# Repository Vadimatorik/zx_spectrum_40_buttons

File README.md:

# zx_spectrum_40_buttons
Репозиторий содержит в себе файлы проекта и файлы производства клавиатуры в 40 клавиш для подключения к ZX Spectrum совместимым компьютерам. В качестве клавиш используются Cherry MX.

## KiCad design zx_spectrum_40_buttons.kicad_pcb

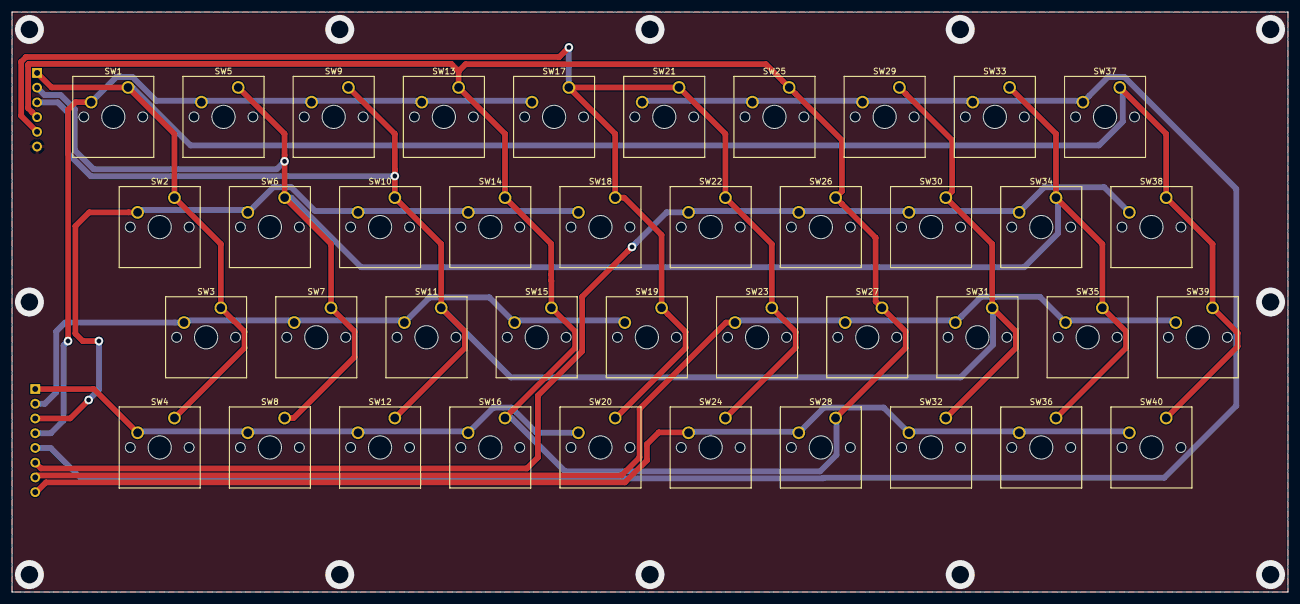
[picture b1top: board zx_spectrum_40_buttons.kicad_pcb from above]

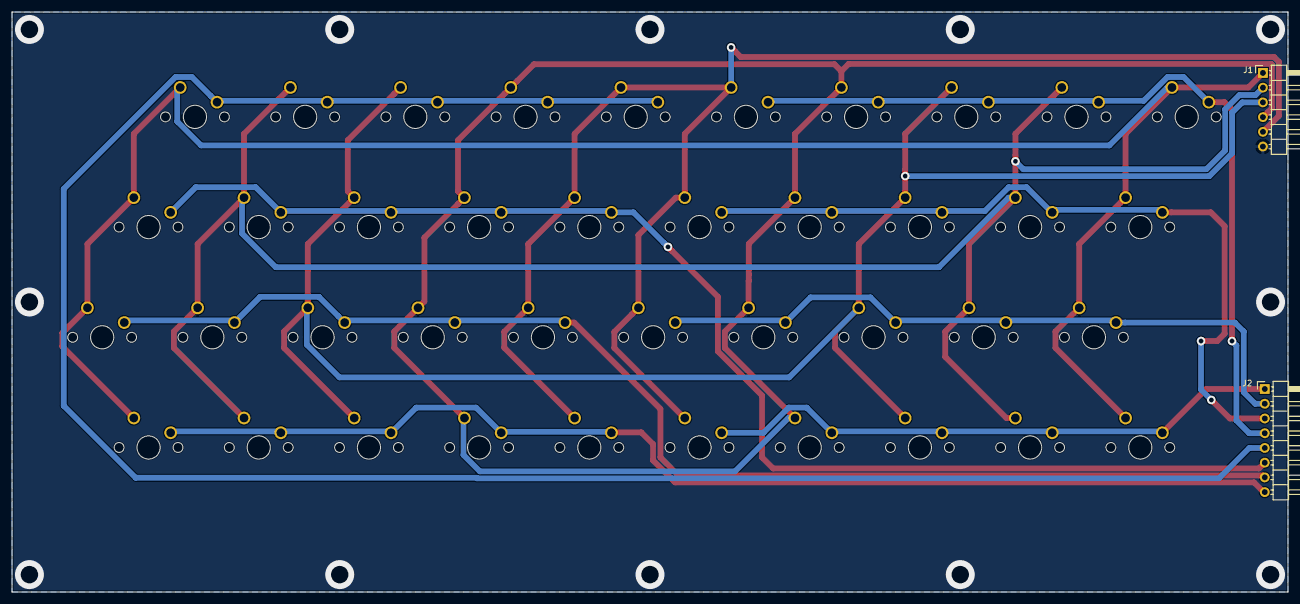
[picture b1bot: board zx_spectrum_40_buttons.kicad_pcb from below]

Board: 2 copper layers, 220.0 x 100.0 mm, 42 parts (2 on the bottom side), 13 nets.

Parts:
J1: column; PinHeader_1x06_P2.54mm_Horizontal
J2: str; PinHeader_1x08_P2.54mm_Horizontal
SW1: 1; SW_Cherry_MX_1.00u_PCB
SW2: Q; SW_Cherry_MX_1.00u_PCB
SW3: A; SW_Cherry_MX_1.00u_PCB
SW4: C.S.; SW_Cherry_MX_1.00u_PCB
SW5: 2; SW_Cherry_MX_1.00u_PCB
SW6: W; SW_Cherry_MX_1.00u_PCB
SW7: S; SW_Cherry_MX_1.00u_PCB
SW8: Z; SW_Cherry_MX_1.00u_PCB
SW9: 3; SW_Cherry_MX_1.00u_PCB
SW10: E; SW_Cherry_MX_1.00u_PCB
SW11: D; SW_Cherry_MX_1.00u_PCB
SW12: X; SW_Cherry_MX_1.00u_PCB
SW13: 4; SW_Cherry_MX_1.00u_PCB
SW14: R; SW_Cherry_MX_1.00u_PCB
SW15: F; SW_Cherry_MX_1.00u_PCB
SW16: C; SW_Cherry_MX_1.00u_PCB
SW17: 5; SW_Cherry_MX_1.00u_PCB
SW18: T; SW_Cherry_MX_1.00u_PCB
SW19: G; SW_Cherry_MX_1.00u_PCB
SW20: V; SW_Cherry_MX_1.00u_PCB
SW21: 6; SW_Cherry_MX_1.00u_PCB
SW22: Y; SW_Cherry_MX_1.00u_PCB
SW23: H; SW_Cherry_MX_1.00u_PCB
SW24: B; SW_Cherry_MX_1.00u_PCB
SW25: 7; SW_Cherry_MX_1.00u_PCB
SW26: U; SW_Cherry_MX_1.00u_PCB
SW27: J; SW_Cherry_MX_1.00u_PCB
SW28: N; SW_Cherry_MX_1.00u_PCB
SW29: 8; SW_Cherry_MX_1.00u_PCB
SW30: I; SW_Cherry_MX_1.00u_PCB
SW31: K; SW_Cherry_MX_1.00u_PCB
SW32: M; SW_Cherry_MX_1.00u_PCB
SW33: 9; SW_Cherry_MX_1.00u_PCB
SW34: O; SW_Cherry_MX_1.00u_PCB
SW35: L; SW_Cherry_MX_1.00u_PCB
SW36: S.S.; SW_Cherry_MX_1.00u_PCB
SW37: 10; SW_Cherry_MX_1.00u_PCB
SW38: P; SW_Cherry_MX_1.00u_PCB
SW39: ENTER; SW_Cherry_MX_1.00u_PCB
SW40: SPACE; SW_Cherry_MX_1.00u_PCB

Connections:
/column_1: J1.1, SW1.1, SW2.1, SW3.1, SW4.1, SW37.1, SW38.1, SW39.1, SW40.1
/column_2: J1.2, SW5.1, SW6.1, SW7.1, SW8.1, SW33.1, SW34.1, SW35.1, SW36.1
/column_3: J1.3, SW9.1, SW10.1, SW11.1, SW12.1, SW29.1, SW30.1, SW31.1, SW32.1
/column_4: J1.4, SW13.1, SW14.1, SW15.1, SW16.1, SW25.1, SW26.1, SW27.1, SW28.1
/column_5: J1.5, SW17.1, SW18.1, SW19.1, SW20.1, SW21.1, SW22.1, SW23.1, SW24.1
/str_1: J2.1, SW4.2, SW8.2, SW12.2, SW16.2, SW20.2
/str_2: J2.2, SW3.2, SW7.2, SW11.2, SW15.2, SW19.2
/str_3: J2.3, SW2.2, SW6.2, SW10.2, SW14.2, SW18.2
/str_4: J2.4, SW1.2, SW5.2, SW9.2, SW13.2, SW17.2
/str_5: J2.5, SW21.2, SW25.2, SW29.2, SW33.2, SW37.2
/str_6: J2.6, SW22.2, SW26.2, SW30.2, SW34.2, SW38.2
/str_7: J2.7, SW23.2, SW27.2, SW31.2, SW35.2, SW39.2
/str_8: J2.8, SW24.2, SW28.2, SW32.2, SW36.2, SW40.2

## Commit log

2020-04-17 Добавлены файлы проекта.
2020-04-17 Добавлен STEP.
2020-04-17 Добавил png.
2020-04-21 Заменил модели клавиш.
2020-04-26 +10 см снизу для креплений.
